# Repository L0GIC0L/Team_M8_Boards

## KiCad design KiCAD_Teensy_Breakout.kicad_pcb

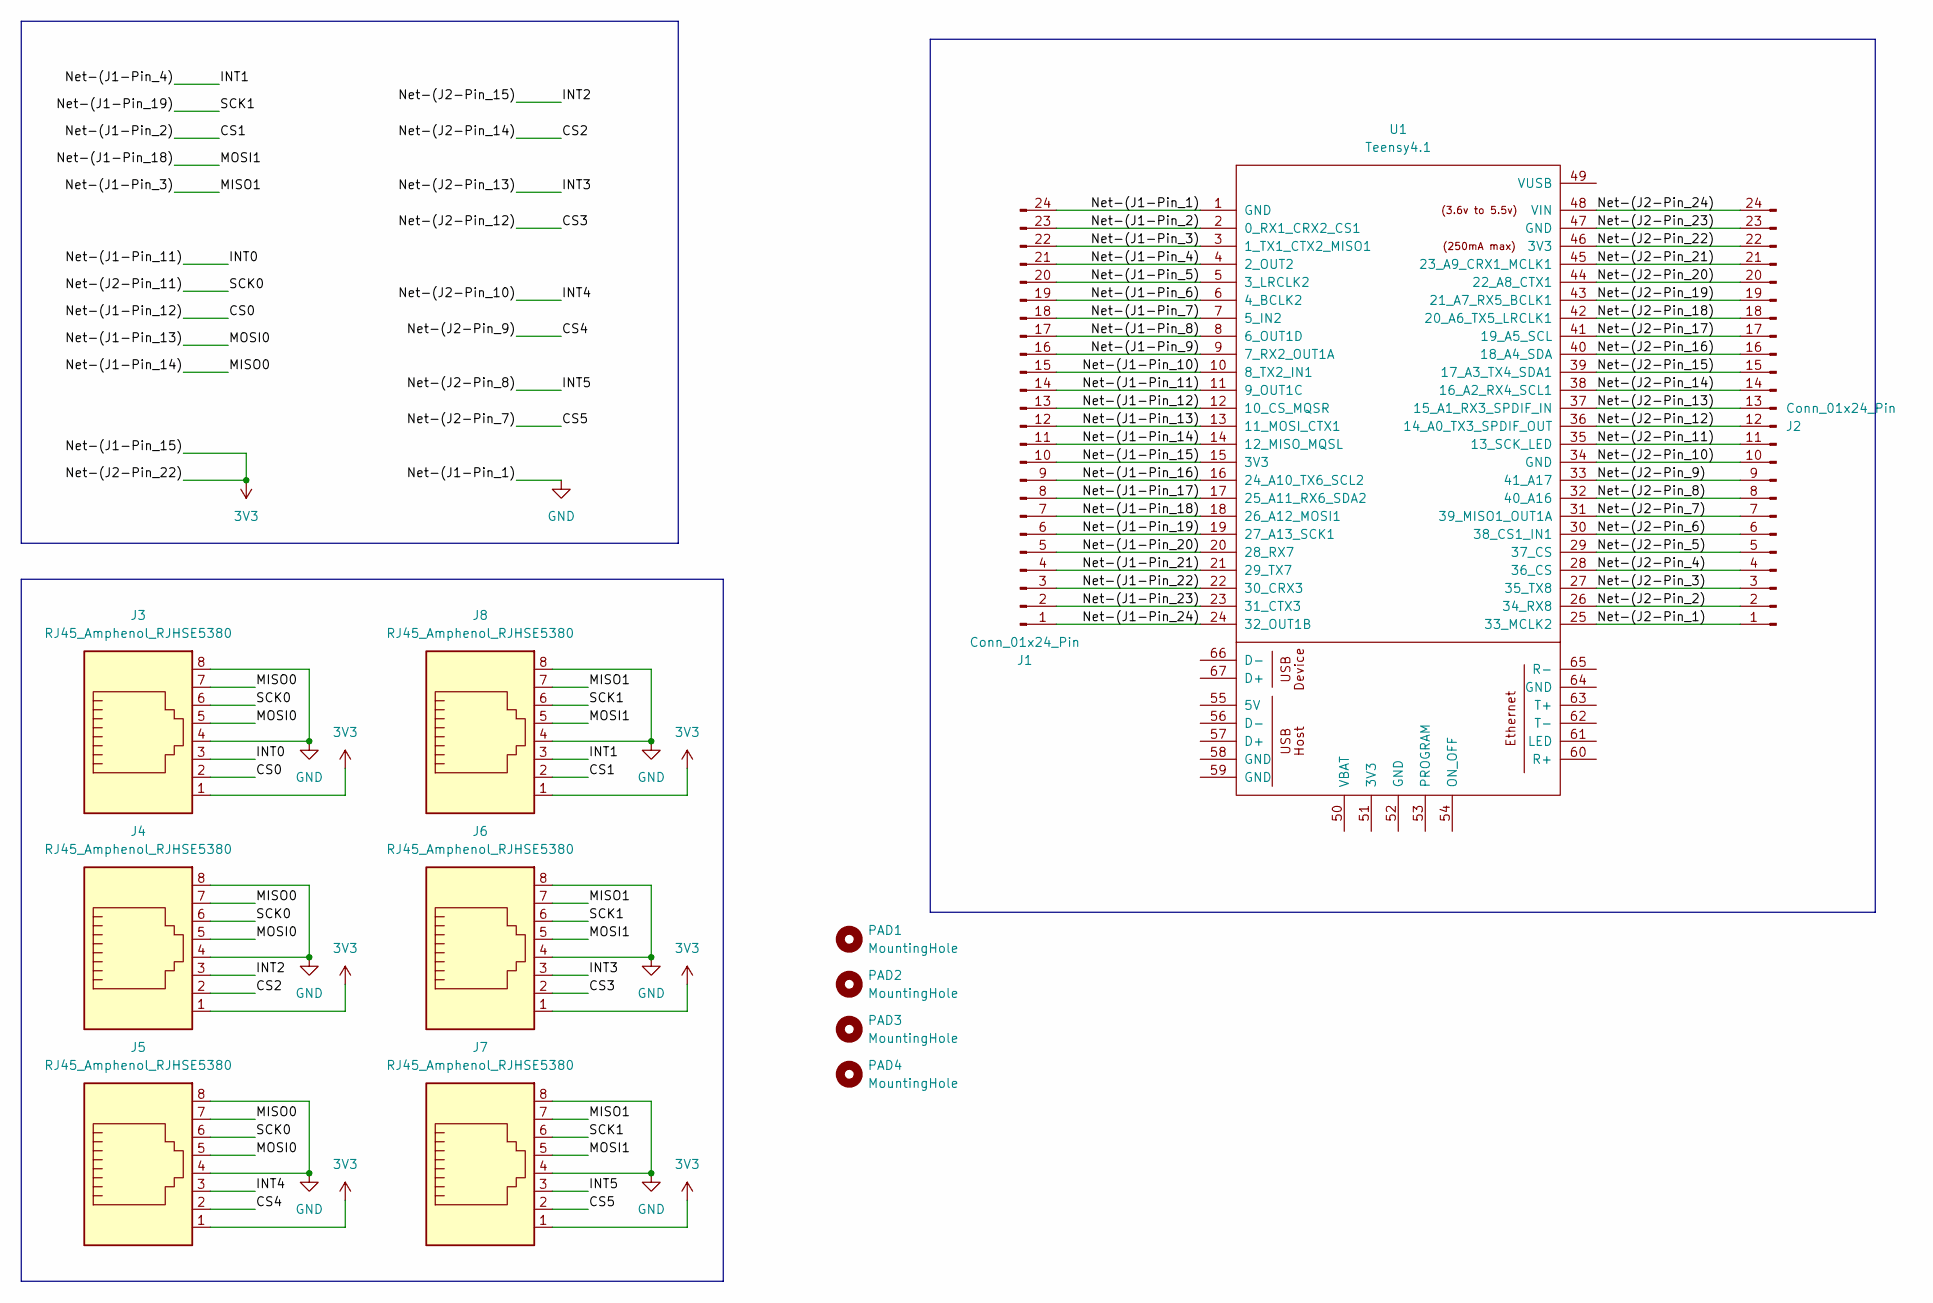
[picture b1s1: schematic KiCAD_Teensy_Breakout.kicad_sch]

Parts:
J1, J2: Conn_01x24_Pin; PinHeader_1x24_P2.54mm_Vertical
J3, J4, J5, J6, J7, J8: RJ45_Amphenol_RJHSE5380
PAD1, PAD2, PAD3, PAD4: MountingHole; MountingHole_2.2mm_M2_Pad_Via
U1: Teensy4.1; Teensy41

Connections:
3V3: J1.10, J2.22, J3.1, J4.1, J5.1, J6.1, J7.1, J8.1, U1.15 (3V3), U1.46 (3V3)
/CS0: J1.13, J3.2, U1.12 (10_CS_MQSR)
/CS1: J1.23, J8.2, U1.2 (0_RX1_CRX2_CS1)
/CS2: J2.14, J4.2, U1.38 (16_A2_RX4_SCL1)
/CS3: J2.12, J6.2, U1.36 (14_A0_TX3_SPDIF_OUT)
/CS4: J2.9, J5.2, U1.33 (41_A17)
/CS5: J2.7, J7.2, U1.31 (39_MISO1_OUT1A)
/INT0: J1.14, J3.3, U1.11 (9_OUT1C)
/INT1: J1.21, J8.3, U1.4 (2_OUT2)
/INT2: J2.15, J4.3, U1.39 (17_A3_TX4_SDA1)
/INT3: J2.13, J6.3, U1.37 (15_A1_RX3_SPDIF_IN)
/INT4: J2.10, J5.3, U1.34 (GND)
/INT5: J2.8, J7.3, U1.32 (40_A16)
/MISO0: J1.11, J3.7, J4.7, J5.7, U1.14 (12_MISO_MQSL)
/MISO1: J1.22, J6.7, J7.7, J8.7, U1.3 (1_TX1_CTX2_MISO1)
/MOSI0: J1.12, J3.5, J4.5, J5.5, U1.13 (11_MOSI_CTX1)
/MOSI1: J1.7, J6.5, J7.5, J8.5, U1.18 (26_A12_MOSI1)
/Net-(J1-Pin_5): J1.20, U1.5 (3_LRCLK2)
/Net-(J1-Pin_6): J1.19, U1.6 (4_BCLK2)
/Net-(J1-Pin_7): J1.18, U1.7 (5_IN2)
/Net-(J1-Pin_8): J1.17, U1.8 (6_OUT1D)
/Net-(J1-Pin_9): J1.16, U1.9 (7_RX2_OUT1A)
/Net-(J1-Pin_10): J1.15, U1.10 (8_TX2_IN1)
/Net-(J1-Pin_16): J1.9, U1.16 (24_A10_TX6_SCL2)
/Net-(J1-Pin_17): J1.8, U1.17 (25_A11_RX6_SDA2)
/Net-(J1-Pin_19): J1.6, J6.6, J7.6, J8.6, U1.19 (27_A13_SCK1)
/Net-(J1-Pin_20): J1.5, U1.20 (28_RX7)
/Net-(J1-Pin_21): J1.4, U1.21 (29_TX7)
/Net-(J1-Pin_22): J1.3, U1.22 (30_CRX3)
/Net-(J1-Pin_23): J1.2, U1.23 (31_CTX3)
/Net-(J1-Pin_24): J1.1, U1.24 (32_OUT1B)
/Net-(J2-Pin_1): J2.1, U1.25 (33_MCLK2)
/Net-(J2-Pin_2): J2.2, U1.26 (34_RX8)
/Net-(J2-Pin_3): J2.3, U1.27 (35_TX8)
/Net-(J2-Pin_4): J2.4, U1.28 (36_CS)
/Net-(J2-Pin_5): J2.5, U1.29 (37_CS)
/Net-(J2-Pin_6): J2.6, U1.30 (38_CS1_IN1)
/Net-(J2-Pin_11): J2.11, J3.6, J4.6, J5.6, U1.35 (13_SCK_LED)
/Net-(J2-Pin_16): J2.16, U1.40 (18_A4_SDA)
/Net-(J2-Pin_17): J2.17, U1.41 (19_A5_SCL)
/Net-(J2-Pin_18): J2.18, U1.42 (20_A6_TX5_LRCLK1)
/Net-(J2-Pin_19): J2.19, U1.43 (21_A7_RX5_BCLK1)
/Net-(J2-Pin_20): J2.20, U1.44 (22_A8_CTX1)
/Net-(J2-Pin_21): J2.21, U1.45 (23_A9_CRX1_MCLK1)
/Net-(J2-Pin_23): J2.23, U1.47 (GND)
/Net-(J2-Pin_24): J2.24, U1.48 (VIN)
GND: J1.24, J3.4, J3.8, J4.4, J4.8, J5.4, J5.8, J6.4, J6.8, J7.4, J7.8, J8.4, J8.8, U1.1 (GND)

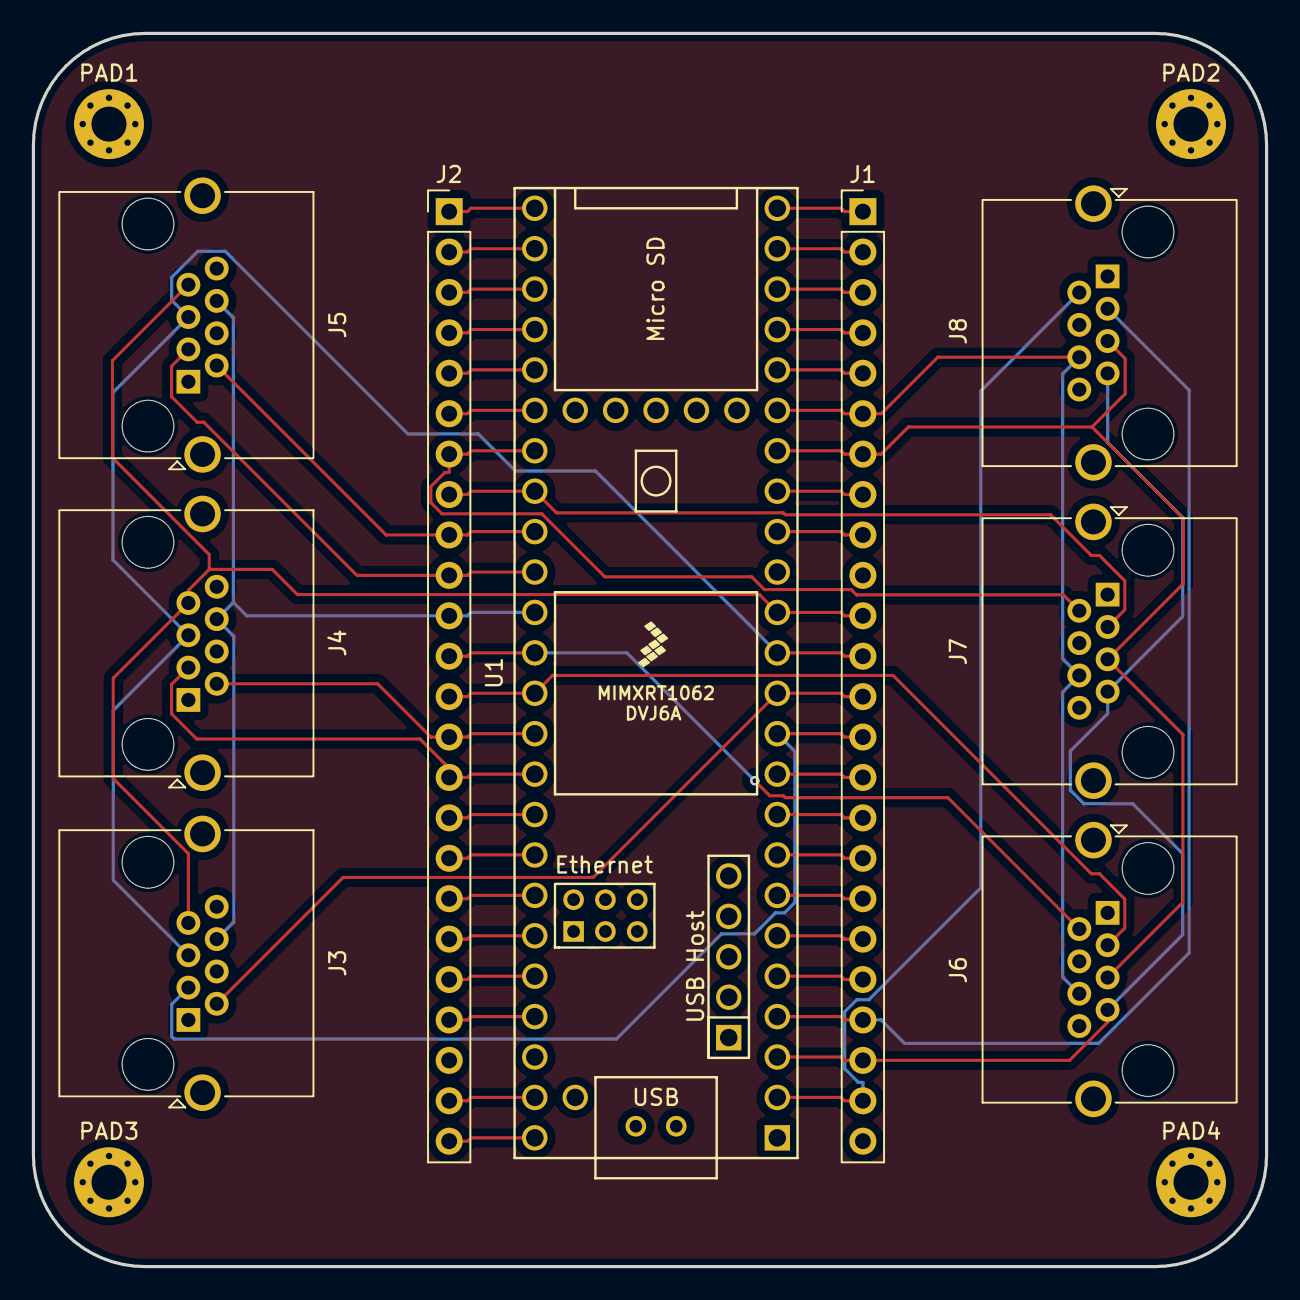
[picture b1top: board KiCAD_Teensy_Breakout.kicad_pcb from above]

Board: 4 copper layers, 77.5 x 77.5 mm, 13 parts (0 on the bottom side), 47 nets.

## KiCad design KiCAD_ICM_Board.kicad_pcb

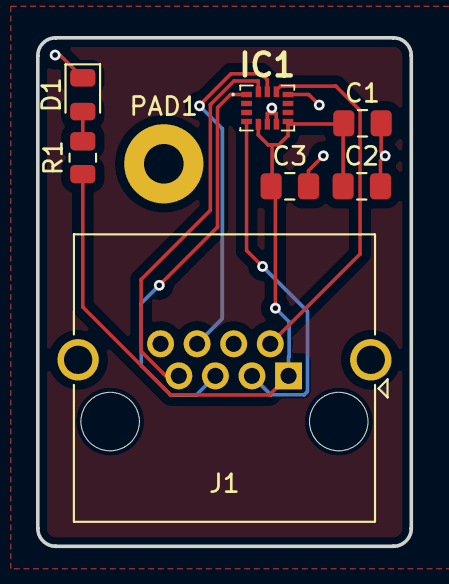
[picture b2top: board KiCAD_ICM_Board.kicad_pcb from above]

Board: 2 copper layers, 20.8 x 28.2 mm, 8 parts (0 on the bottom side), 8 nets.

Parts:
C1: 2.2uF; C_0805_2012Metric_Pad1.18x1.45mm_HandSolder
C2: 0.1uF; C_0805_2012Metric_Pad1.18x1.45mm_HandSolder
C3: 10nF; C_0805_2012Metric_Pad1.18x1.45mm_HandSolder
D1: LED; LED_0805_2012Metric
IC1: ICM-42688-P; IIM42352
J1: RJ45; RJ45_Amphenol_RJHSE5380
PAD1: MountingHole_2.2mm_M2_Pad
R1: 47ohm; R_0805_2012Metric

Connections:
/Net-(IC1-VDD): C1.1, C2.1, C3.1, IC1.5 (VDDIO), IC1.8 (VDD), J1.1, R1.1
/unconnected-(IC1-AP_CS-Pad12): IC1.12 (AP_CS), J1.2
/unconnected-(IC1-AP_SCL_/_AP_SCLK-Pad13): IC1.13 (AP_SCL_/_AP_SCLK), J1.6
/unconnected-(IC1-AP_SDA_/_AP_SDIO_/_AP_SDI-Pad14): IC1.14 (AP_SDA_/_AP_SDIO_/_AP_SDI), J1.7
/unconnected-(IC1-AP_SDO_/_AP_AD0-Pad1): IC1.1 (AP_SDO_/_AP_AD0), J1.5
/unconnected-(IC1-INT1_/_INT-Pad4): IC1.4 (INT1_/_INT), J1.3
GNDPWR: C1.2, C2.2, C3.2, D1.1 (K), IC1.6 (GND), IC1.7 (RESV_3), IC1.11 (RESV_5), J1.4, J1.8
unnamed: D1.2 (A), R1.2

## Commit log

2024-10-28 Wipe branch and upload new folder content
